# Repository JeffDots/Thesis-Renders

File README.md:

# Thesis-Renders
Version Control for kicad and others

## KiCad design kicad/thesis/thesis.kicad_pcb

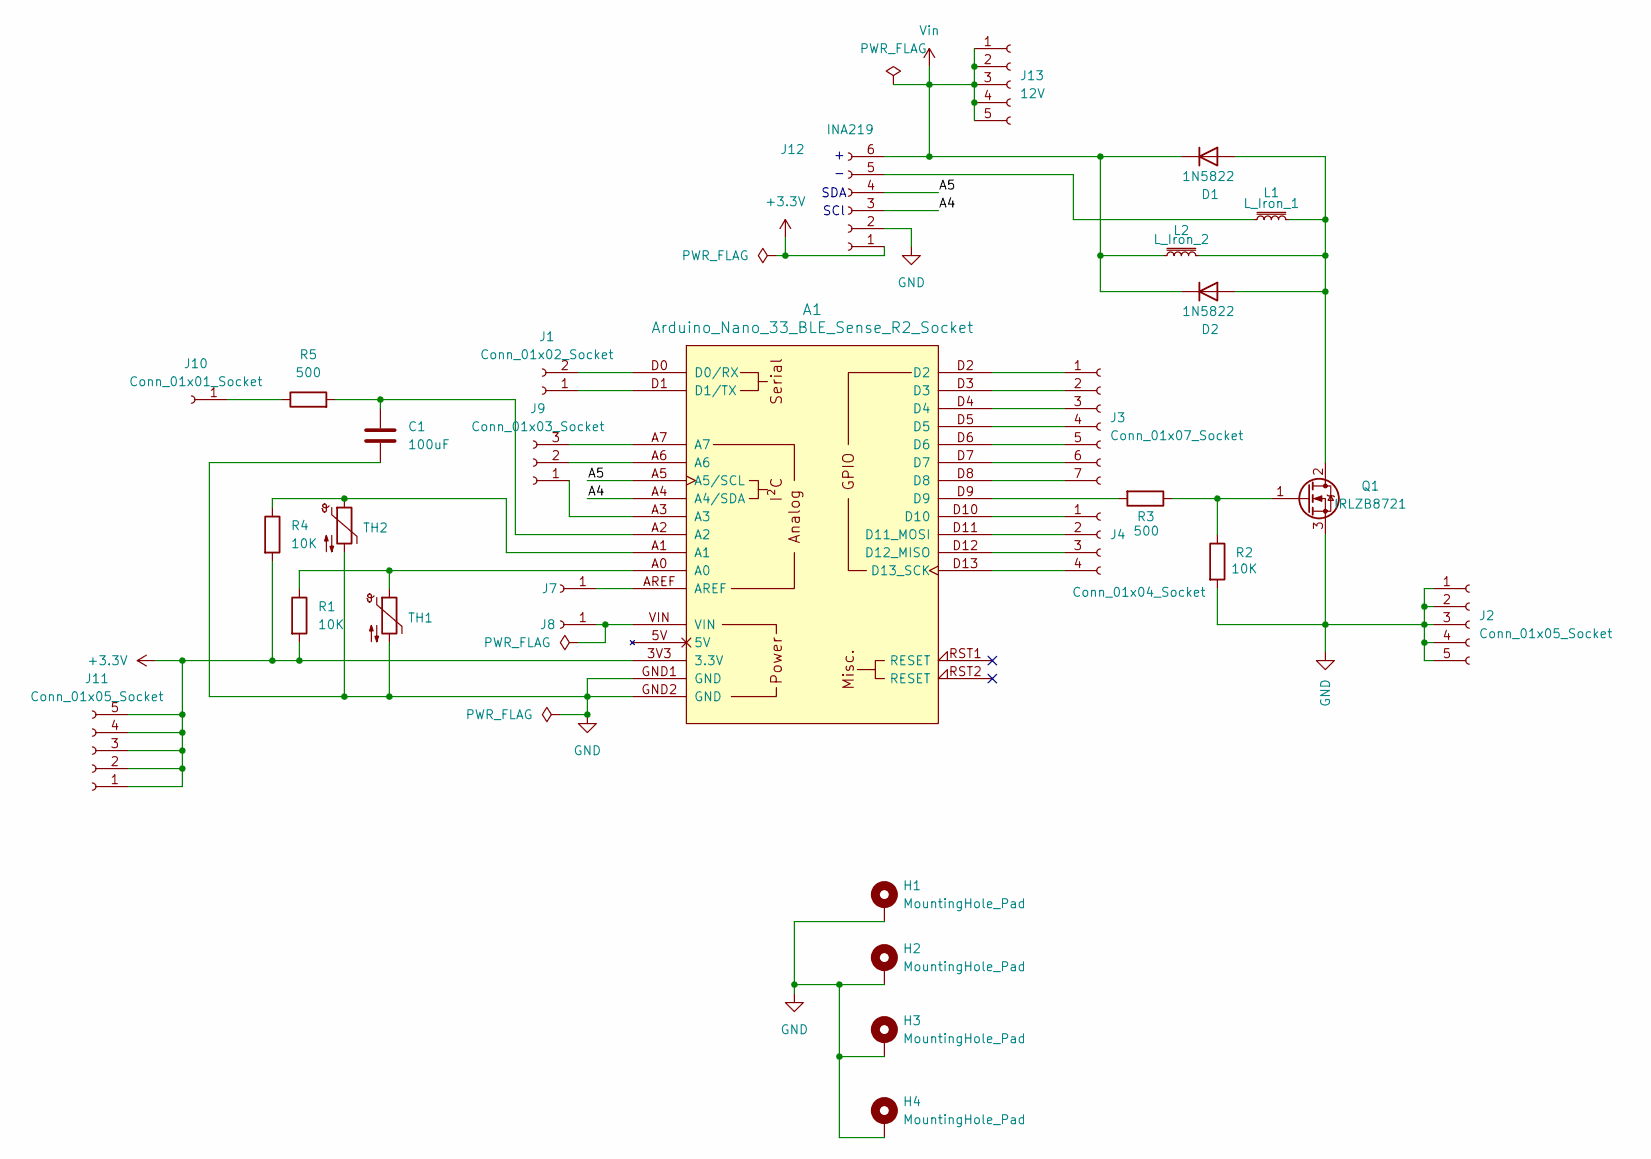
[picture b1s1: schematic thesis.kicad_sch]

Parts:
A1: Arduino_Nano_33_BLE_Sense_R2_Socket; Arduino_Nano_Every_Socket
C1: 100uF; C_Radial_D6.3mm_H7.0mm_P2.50mm
D1, D2: 1N5822; D_DO-201AD_P15.24mm_Horizontal
H1, H2, H3, H4: MountingHole_Pad; MountingHole_2.5mm_Pad
J1: Conn_01x02_Socket; PinSocket_1x02_P2.54mm_Vertical
J2, J11: Conn_01x05_Socket; PinSocket_1x05_P2.54mm_Vertical
J3: Conn_01x07_Socket; PinSocket_1x07_P2.54mm_Vertical
J4: Conn_01x04_Socket; PinSocket_1x04_P2.54mm_Vertical
J7, J8, J10: Conn_01x01_Socket; PinSocket_1x01_P2.54mm_Vertical
J9: Conn_01x03_Socket; PinSocket_1x03_P2.54mm_Vertical
J12: INA219; PinSocket_1x06_P2.54mm_Vertical
J13: 12V; PinSocket_1x05_P2.54mm_Vertical
L1: L_Iron_1; TerminalBlock_Phoenix_MKDS-1,5-2-5.08_1x02_P5.08mm_Horizont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
L2: L_Iron_2; TerminalBlock_Phoenix_MKDS-1,5-2-5.08_1x02_P5.08mm_Horizont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
Q1: IRLZB8721; TO-220-3_Vertical
R1, R2, R4: 10K; R_Axial_DIN0204_L3.6mm_D1.6mm_P7.62mm_Horizontal
R3, R5: 500; R_Axial_DIN0204_L3.6mm_D1.6mm_P7.62mm_Horizontal
TH1, TH2: Thermistor_NTC; TerminalBlock_Phoenix_MKDS-1,5-2-5.08_1x02_P5.08mm_Horizont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

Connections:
+3.3V: A1.3V3 (3.3V), J11.1, J11.2, J11.3, J11.4, J11.5, J12.1, R1.2, R4.2
/A4: A1.A4 (A4/SDA), J12.3
/A5: A1.A5 (A5/SCL), J12.4
GND: A1.GND1 (GND), A1.GND2 (GND), C1.2, H1.1 (1_1), H2.1 (1_1), H3.1 (1_1), H4.1 (1_1), J2.1, J2.2, J2.3, J2.4, J2.5, J12.2, Q1.3 (S), R2.2, TH1.2, TH2.2
unnamed: A1.D0 (D0/RX), J1.2
unnamed: A1.D1 (D1/TX), J1.1
unnamed: A1.D11 (D11_MOSI), J4.2
unnamed: A1.D12 (D12_MISO), J4.3
unnamed: A1.D13 (D13_SCK), J4.4
unnamed: A1.A0, R1.1, TH1.1
unnamed: A1.A1, R4.1, TH2.1
unnamed: A1.A2, C1.1, R5.2
unnamed: A1.D9, R3.2
unnamed 13: D1.2 (A), D2.2 (A), L1.2, L2.2, Q1.2 (D); also elsewhere on the board
unnamed: A1.D2, J3.1
unnamed: A1.D3, J3.2
unnamed: A1.D4, J3.3
unnamed: A1.D5, J3.4
unnamed: A1.D6, J3.5
unnamed: A1.D7, J3.6
unnamed: A1.D8, J3.7
unnamed: A1.D10, J4.1
unnamed: A1.AREF, J7.1 (Pin_1_1)
unnamed: A1.VIN, J8.1 (Pin_1_1)
unnamed: A1.A3, J9.1
unnamed: A1.A6, J9.2
unnamed: A1.A7, J9.3
unnamed: J10.1 (Pin_1_1), R5.1
unnamed 28: J12.5, L1.1; also elsewhere on the board
unnamed: Q1.1 (G), R2.1, R3.1
Vin: D1.1 (K), D2.1 (K), J12.6, J13.1, J13.2, J13.3, J13.4, J13.5, L2.1; also elsewhere on the board

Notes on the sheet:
SCl
SDA

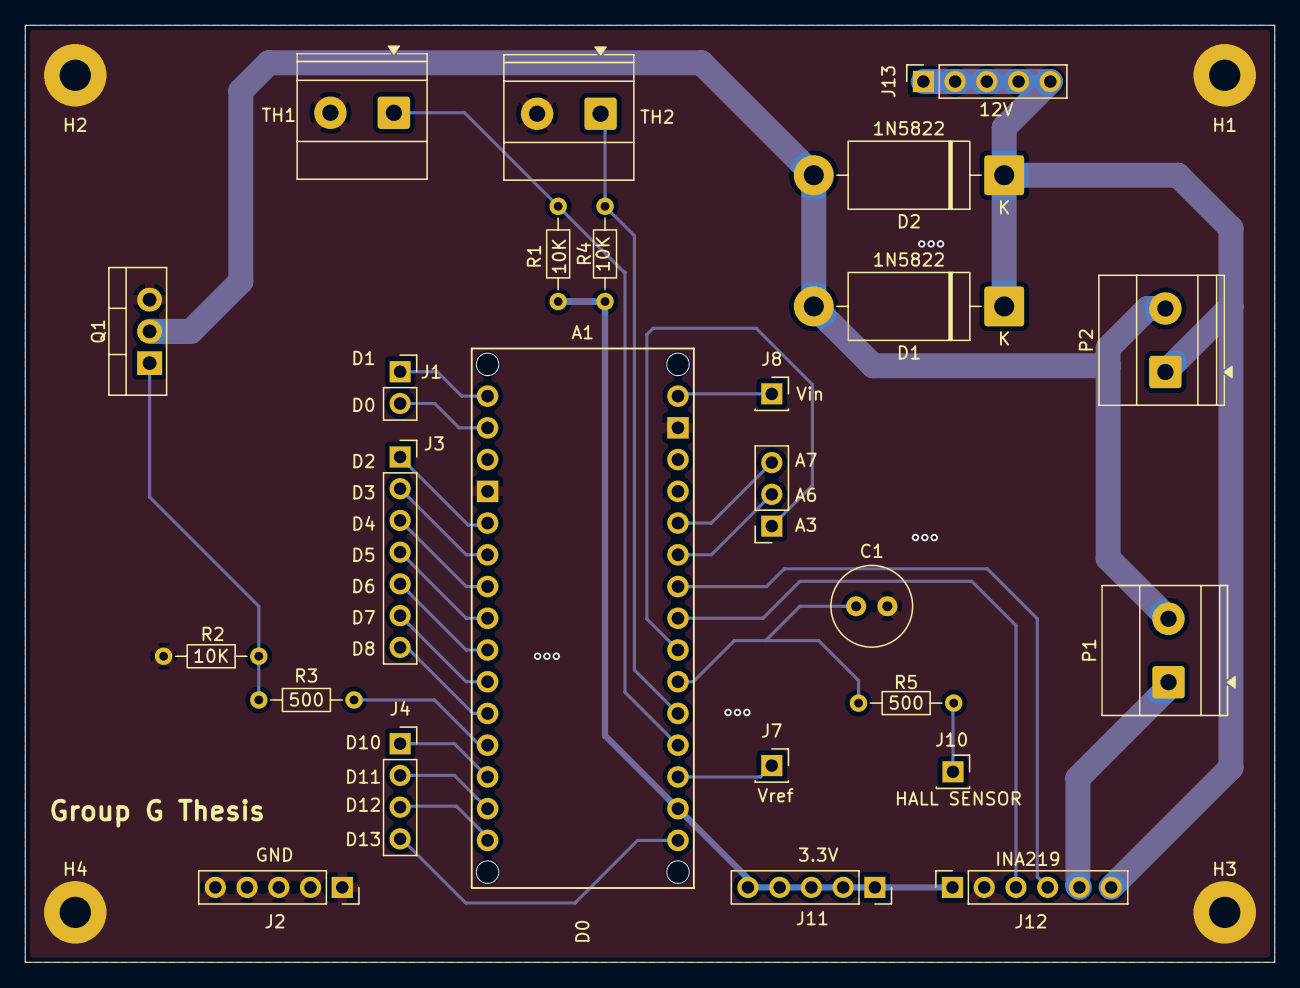
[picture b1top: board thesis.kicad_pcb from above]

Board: 2 copper layers, 100.0 x 75.0 mm, 29 parts (0 on the bottom side), 31 nets.

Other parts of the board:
P1: L_Iron_1; TerminalBlock_Phoenix_MKDS-1,5-2-5.08_1x02_P5.08mm_Horizont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
P2: L_Iron_2; TerminalBlock_Phoenix_MKDS-1,5-2-5.08_1x02_P5.08mm_Horizont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

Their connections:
unnamed 13: P1.2, P2.2; also elsewhere on the board
unnamed 28: P1.1; also elsewhere on the board
Vin: P2.1; also elsewhere on the board
